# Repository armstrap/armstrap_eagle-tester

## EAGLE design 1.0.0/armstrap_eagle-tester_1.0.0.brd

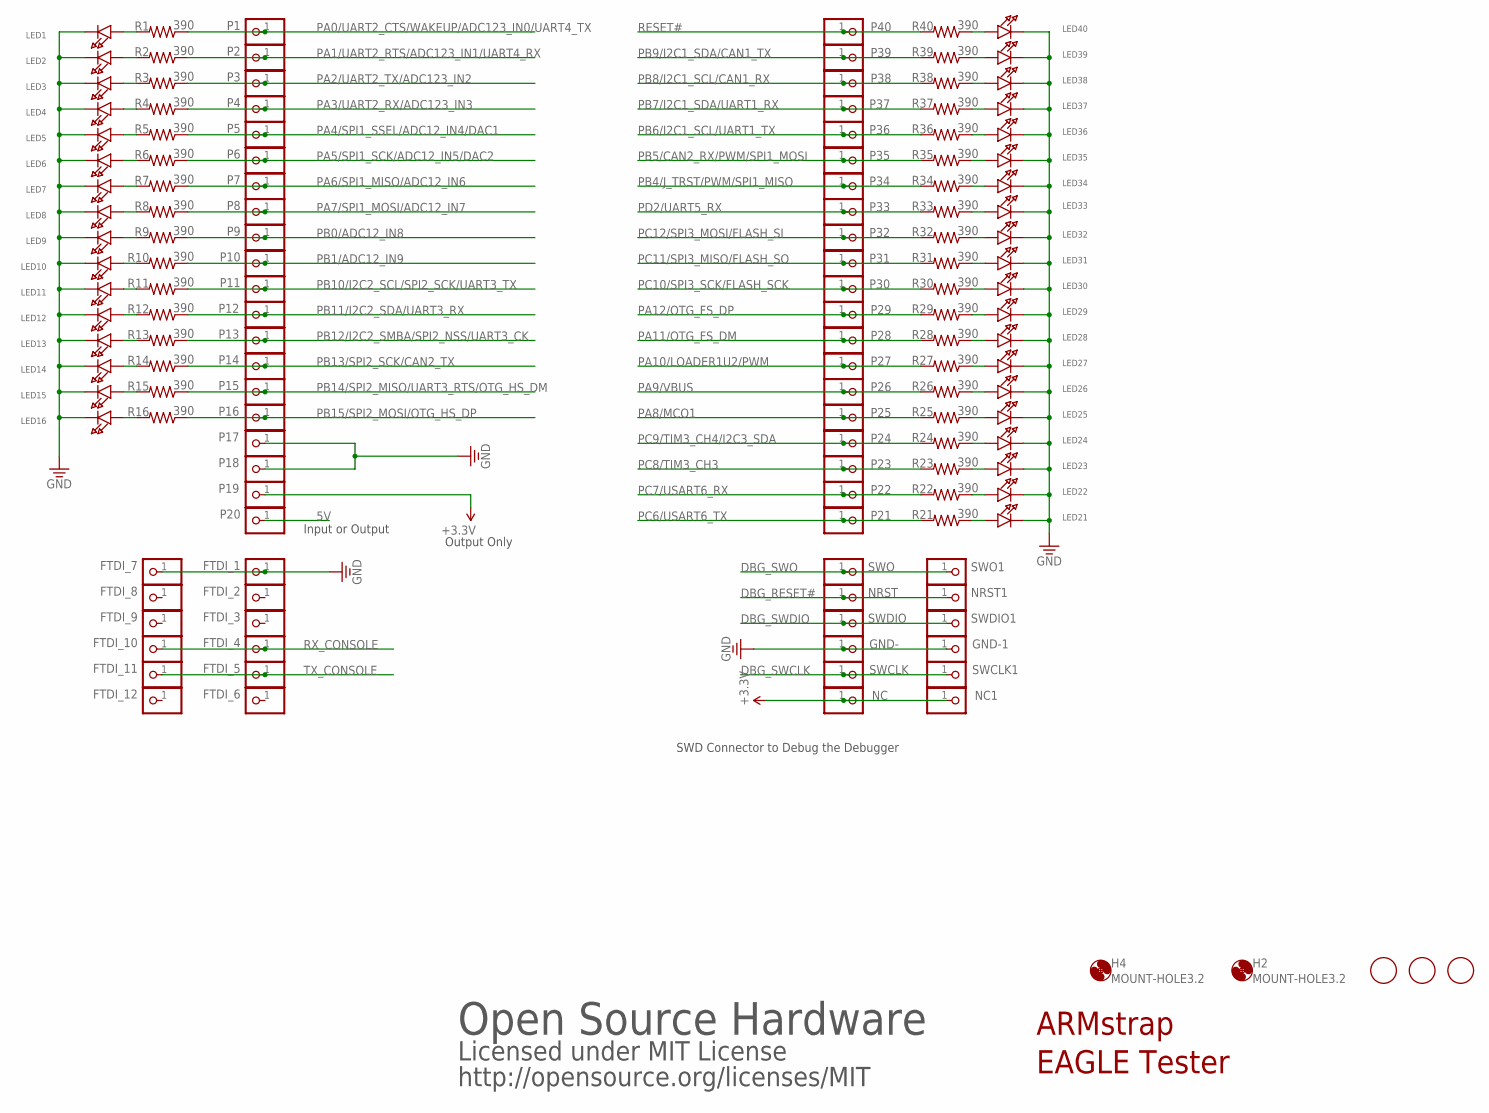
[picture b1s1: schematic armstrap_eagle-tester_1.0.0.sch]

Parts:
FID2, FID3, FID4: FIDUCIAL; FIDUCIAL_1MM
FTDI_1, FTDI_2, FTDI_3, FTDI_4, FTDI_5, FTDI_6, FTDI_7, FTDI_8, FTDI_9, FTDI_10, FTDI_11, FTDI_12: PINHD-1X1; 1X01
GND-, GND-1: PINHD-1X1; 1X01
H2, H4: MOUNT-HOLE3.2; 3,2
LED1, LED2, LED3, LED4, LED5, LED6, LED7, LED8, LED9, LED10, LED11, LED12, LED13, LED14, LED15, LED16, LED21, LED22, LED23, LED24, LED25, LED26, LED27, LED28, LED29, LED30, LED31, LED32, LED33, LED34, LED35, LED36, LED37, LED38, LED39, LED40: APT3216QBC/D; CHIPLED_1206
NC, NC1: PINHD-1X1; 1X01
NRST, NRST1: PINHD-1X1; 1X01
P1, P2, P3, P4, P5, P6, P7, P8, P9, P10, P11, P12, P13, P14, P15, P16, P17, P18, P19, P20, P21, P22, P23, P24, P25, P26, P27, P28, P29, P30, P31, P32, P33, P34, P35, P36, P37, P38, P39, P40: PINHD-1X1; 1X01
R1, R2, R3, R4, R5, R6, R7, R8, R9, R10, R11, R12, R13, R14, R15, R16, R21, R22, R23, R24, R25, R26, R27, R28, R29, R30, R31, R32, R33, R34, R35, R36, R37, R38, R39, R40: 390; 0805
SWCLK, SWCLK1: PINHD-1X1; 1X01
SWDIO, SWDIO1: PINHD-1X1; 1X01
SWO, SWO1: PINHD-1X1; 1X01

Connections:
3.3V: NC.1, NC1.1, P19.1
5: LED5.A, R5.2
5V: P20.1
11: LED11.A, R11.2
DBG_RESET#: NRST.1, NRST1.1
DBG_SWCLK: SWCLK.1, SWCLK1.1
DBG_SWDIO: SWDIO.1, SWDIO1.1
DBG_SWO: SWO.1, SWO1.1
E2: LED2.A, R2.2
GND: FTDI_1.1, FTDI_7.1, GND-.1, GND-1.1, LED1.C, LED2.C, LED3.C, LED4.C, LED5.C, LED6.C, LED7.C, LED8.C, LED9.C, LED10.C, LED11.C, LED12.C, LED13.C, LED14.C, LED15.C, LED16.C, LED21.C, LED22.C, LED23.C, LED24.C, LED25.C, LED26.C, LED27.C, LED28.C, LED29.C, LED30.C, LED31.C, LED32.C, LED33.C, LED34.C, LED35.C, LED36.C, LED37.C, LED38.C, LED39.C, LED40.C, P17.1, P18.1
unnamed: LED1.A, R1.2
unnamed: LED3.A, R3.2
unnamed: LED4.A, R4.2
unnamed: LED6.A, R6.2
unnamed: LED7.A, R7.2
unnamed: LED8.A, R8.2
unnamed: LED9.A, R9.2
unnamed: LED10.A, R10.2
unnamed: LED12.A, R12.2
unnamed: LED13.A, R13.2
unnamed: LED14.A, R14.2
unnamed: LED15.A, R15.2
unnamed: LED16.A, R16.2
unnamed: LED40.A, R40.1
unnamed: LED39.A, R39.1
unnamed: LED38.A, R38.1
unnamed: LED37.A, R37.1
unnamed: LED36.A, R36.1
unnamed: LED35.A, R35.1
unnamed: LED34.A, R34.1
unnamed: LED33.A, R33.1
unnamed: LED32.A, R32.1
unnamed: LED31.A, R31.1
unnamed: LED30.A, R30.1
unnamed: LED29.A, R29.1
unnamed: LED28.A, R28.1
unnamed: LED27.A, R27.1
unnamed: LED26.A, R26.1
unnamed: LED25.A, R25.1
unnamed: LED24.A, R24.1
unnamed: LED23.A, R23.1
unnamed: LED22.A, R22.1
unnamed: LED21.A, R21.1
PA0/UART2_CTS/WAKEUP/ADC123_IN0/UART4_TX: P1.1, R1.1
PA1/UART2_RTS/ADC123_IN1/UART4_RX: P2.1, R2.1
PA2/UART2_TX/ADC123_IN2: P3.1, R3.1
PA3/UART2_RX/ADC123_IN3: P4.1, R4.1
PA4/SPI1_SSEL/ADC12_IN4/DAC1: P5.1, R5.1
PA5/SPI1_SCK/ADC12_IN5/DAC2: P6.1, R6.1
PA6/SPI1_MISO/ADC12_IN6: P7.1, R7.1
PA7/SPI1_MOSI/ADC12_IN7: P8.1, R8.1
PA8/MCO1: P25.1, R25.2
PA9/VBUS: P26.1, R26.2
PA10/LOADER1U2/PWM: P27.1, R27.2
PA11/OTG_FS_DM: P28.1, R28.2
PA12/OTG_FS_DP: P29.1, R29.2
PB0/ADC12_IN8: P9.1, R9.1
PB1/ADC12_IN9: P10.1, R10.1
PB4/J_TRST/PWM/SPI1_MISO: P34.1, R34.2
PB5/CAN2_RX/PWM/SPI1_MOSI: P35.1, R35.2
PB6/I2C1_SCL/UART1_TX: P36.1, R36.2
PB7/I2C1_SDA/UART1_RX: P37.1, R37.2
PB8/I2C1_SCL/CAN1_RX: P38.1, R38.2
PB9/I2C1_SDA/CAN1_TX: P39.1, R39.2
PB10/I2C2_SCL/SPI2_SCK/UART3_TX: P11.1, R11.1
PB11/I2C2_SDA/UART3_RX: P12.1, R12.1
PB12/I2C2_SMBA/SPI2_NSS/UART3_CK: P13.1, R13.1
PB13/SPI2_SCK/CAN2_TX: P14.1, R14.1
PB14/SPI2_MISO/UART3_RTS/OTG_HS_DM: P15.1, R15.1
PB15/SPI2_MOSI/OTG_HS_DP: P16.1, R16.1
PC6/USART6_TX: P21.1, R21.2
PC7/USART6_RX: P22.1, R22.2
PC8/TIM3_CH3: P23.1, R23.2
PC9/TIM3_CH4/I2C3_SDA: P24.1, R24.2
PC10/SPI3_SCK/FLASH_SCK: P30.1, R30.2
PC11/SPI3_MISO/FLASH_SO: P31.1, R31.2
PC12/SPI3_MOSI/FLASH_SI: P32.1, R32.2
PD2/UART5_RX: P33.1, R33.2
RESET#: P40.1, R40.2
RX_CONSOLE: FTDI_4.1, FTDI_10.1
TX_CONSOLE: FTDI_5.1, FTDI_11.1

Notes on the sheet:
ARMstrap
Open Source Hardware
Licensed under MIT License
http://opensource.org/licenses/MIT
SWD Connector to Debug the Debugger
EAGLE Tester
Input or Output
Output Only

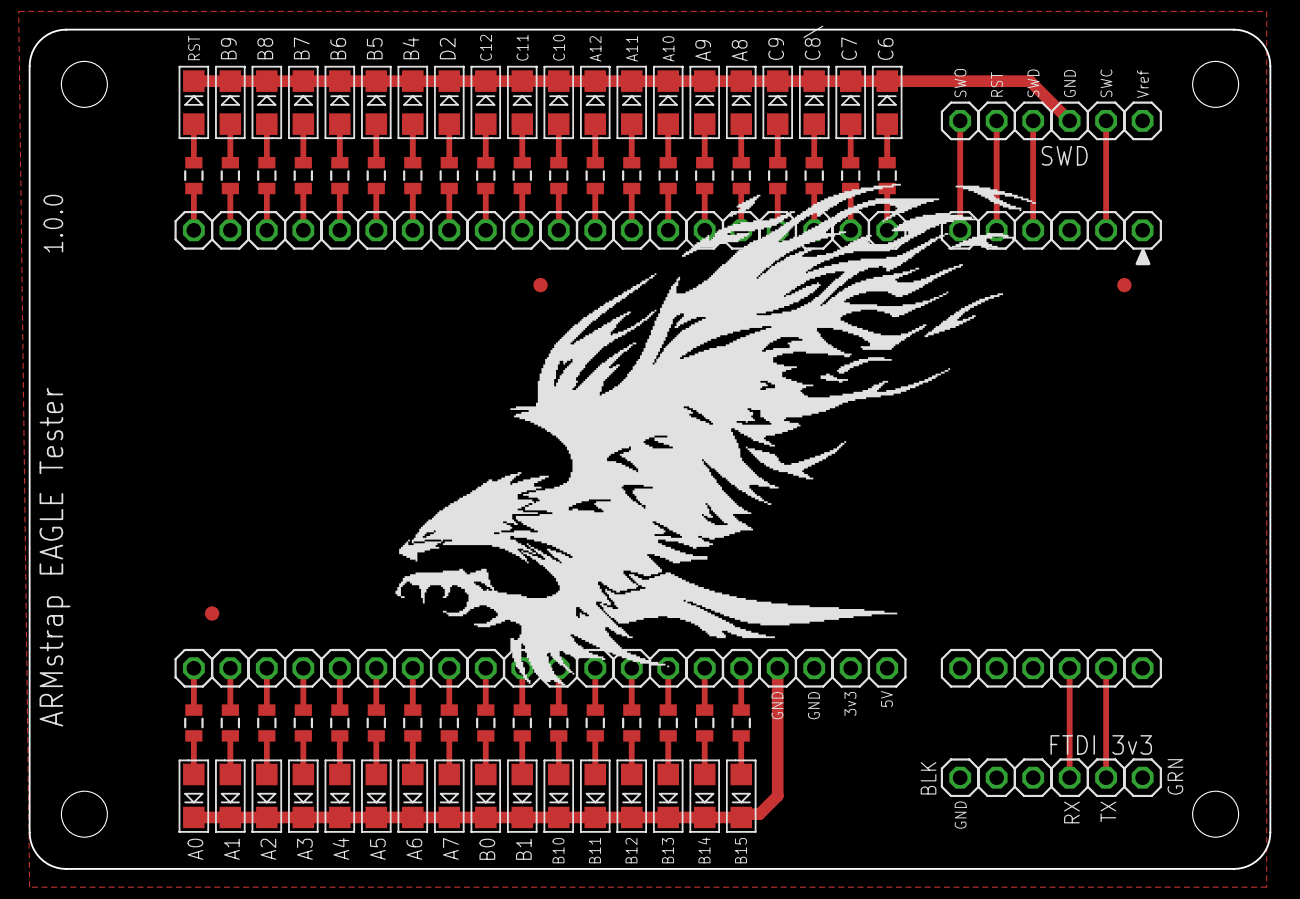
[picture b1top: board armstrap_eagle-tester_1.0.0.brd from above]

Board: 2 copper layers, 86.4 x 58.4 mm, 143 parts (0 on the bottom side), 80 nets.

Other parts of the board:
H1, H3: MOUNT-HOLE3.2; 3,2

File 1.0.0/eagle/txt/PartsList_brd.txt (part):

Partlist

Exported from armstrap_eagle-tester_1.0.0.brd at 12/7/14 9:47 PM

EAGLE Version 6.4.0 Copyright (c) 1988-2013 CadSoft

Assembly variant: 

Part     Value          Package      Library  Position (inch)       Orientation

FID2     FIDUCIAL       FIDUCIAL_1MM vovtech  (3 1.6)               R0
FID3     FIDUCIAL       FIDUCIAL_1MM vovtech  (0.5 0.7)             R0
FID4     FIDUCIAL       FIDUCIAL_1MM vovtech  (1.4 1.6)             R0
FTDI_1                  1X01         pinhead  (2.55 0.55)           R0
FTDI_2                  1X01         pinhead  (2.65 0.55)           R0
FTDI_3                  1X01         pinhead  (2.75 0.55)           R0
FTDI_4                  1X01         pinhead  (2.85 0.55)           R0
FTDI_5                  1X01         pinhead  (2.95 0.55)           R0
FTDI_6                  1X01         pinhead  (3.05 0.55)           R0
FTDI_7                  1X01         pinhead  (2.55 0.25)           R90
FTDI_8                  1X01         pinhead  (2.65 0.25)           R90
FTDI_9                  1X01         pinhead  (2.75 0.25)           R90
FTDI_10                 1X01         pinhead  (2.85 0.25)           R90
FTDI_11                 1X01         pinhead  (2.95 0.25)           R90
FTDI_12                 1X01         pinhead  (3.05 0.25)           R90
GND-                    1X01         pinhead  (2.85 1.75)           R0
GND-1                   1X01         pinhead  (2.85 2.05)           R90
LED1     APT3216QBC/D   CHIPLED_1206 vovtech  (0.45 0.2)            R90
LED2     APT3216QBC/D   CHIPLED_1206 vovtech  (0.55 0.2)            R90
LED3     APT3216QBC/D   CHIPLED_1206 vovtech  (0.65 0.2)            R90
LED4     APT3216QBC/D   CHIPLED_1206 vovtech  (0.75 0.2)            R90
LED5     APT3216QBC/D   CHIPLED_1206 vovtech  (0.85 0.2)            R90
LED6     APT3216QBC/D   CHIPLED_1206 vovtech  (0.95 0.2)            R90
LED7     APT3216QBC/D   CHIPLED_1206 vovtech  (1.05 0.2)            R90
LED8     APT3216QBC/D   CHIPLED_1206 vovtech  (1.15 0.2)            R90
LED9     APT3216QBC/D   CHIPLED_1206 vovtech  (1.25 0.2)            R90
LED10    APT3216QBC/D   CHIPLED_1206 vovtech  (1.35 0.2)            R90
LED11    APT3216QBC/D   CHIPLED_1206 vovtech  (1.45 0.2)            R90
LED12    APT3216QBC/D   CHIPLED_1206 vovtech  (1.55 0.2)            R90
LED13    APT3216QBC/D   CHIPLED_1206 vovtech  (1.65 0.2)            R90
LED14    APT3216QBC/D   CHIPLED_1206 vovtech  (1.75 0.2)            R90
LED15    APT3216QBC/D   CHIPLED_1206 vovtech  (1.85 0.2)            R90
LED16    APT3216QBC/D   CHIPLED_1206 vovtech  (1.95 0.2)            R90
LED21    APT3216QBC/D   CHIPLED_1206 vovtech  (2.35 2.1)            R270
LED22    APT3216QBC/D   CHIPLED_1206 vovtech  (2.25 2.1)            R270
LED23    APT3216QBC/D   CHIPLED_1206 vovtech  (2.15 2.1)            R270
LED24    APT3216QBC/D   CHIPLED_1206 vovtech  (2.05 2.1)            R270
LED25    APT3216QBC/D   CHIPLED_1206 vovtech  (1.95 2.1)            R270
LED26    APT3216QBC/D   CHIPLED_1206 vovtech  (1.85 2.1)            R270
LED27    APT3216QBC/D   CHIPLED_1206 vovtech  (1.75 2.1)            R270
LED28    APT3216QBC/D   CHIPLED_1206 vovtech  (1.65 2.1)            R270
LED29    APT3216QBC/D   CHIPLED_1206 vovtech  (1.55 2.1)            R270
LED30    APT3216QBC/D   CHIPLED_1206 vovtech  (1.45 2.1)            R270
LED31    APT3216QBC/D   CHIPLED_1206 vovtech  (1.35 2.1)            R270
LED32    APT3216QBC/D   CHIPLED_1206 vovtech  (1.25 2.1)            R270
LED33    APT3216QBC/D   CHIPLED_1206 vovtech  (1.15 2.1)            R270
LED34    APT3216QBC/D   CHIPLED_1206 vovtech  (1.05 2.1)            R270
LED35    APT3216QBC/D   CHIPLED_1206 vovtech  (0.95 2.1)            R270
LED36    APT3216QBC/D   CHIPLED_1206 vovtech  (0.85 2.1)            R270
LED37    APT3216QBC/D   CHIPLED_1206 vovtech  (0.75 2.1)            R270
LED38    APT3216QBC/D   CHIPLED_1206 vovtech  (0.65 2.1)            R270
LED39    APT3216QBC/D   CHIPLED_1206 vovtech  (0.55 2.1)            R270
LED40    APT3216QBC/D   CHIPLED_1206 vovtech  (0.45 2.1)            R270
NC                      1X01         pinhead  (3.05 1.75)           R0
NC1                     1X01         pinhead  (3.05 2.05)           R90
NRST                    1X01         pinhead  (2.65 1.75)           R0
NRST1                   1X01         pinhead  (2.65 2.05)           R90
P1                      1X01         pinhead  (0.45 0.55)           R0
P2                      1X01         pinhead  (0.55 0.55)           R90
P3                      1X01         pinhead  (0.65 0.55)           R90
P4                      1X01         pinhead  (0.75 0.55)           R90
P5                      1X01         pinhead  (0.85 0.55)           R90
P6                      1X01         pinhead  (0.95 0.55)           R90
P7                      1X01         pinhead  (1.05 0.55)           R90
P8                      1X01         pinhead  (1.15 0.55)           R90
P9                      1X01         pinhead  (1.25 0.55)           R90
P10                     1X01         pinhead  (1.35 0.55)           R90
P11                     1X01         pinhead  (1.45 0.55)           R90
P12                     1X01         pinhead  (1.55 0.55)           R90
P13                     1X01         pinhead  (1.65 0.55)           R90
P14                     1X01         pinhead  (1.75 0.55)           R90
P15                     1X01         pinhead  (1.85 0.55)           R90
P16                     1X01         pinhead  (1.95 0.55)           R90
P17                     1X01         pinhead  (2.05 0.55)           R90
P18                     1X01         pinhead  (2.15 0.55)           R90
P19                     1X01         pinhead  (2.25 0.55)           R90
P20                     1X01         pinhead  (2.35 0.55)           R90
P21                     1X01         pinhead  (2.35 1.75)           R0
P22                     1X01         pinhead  (2.25 1.75)           R0
P23                     1X01         pinhead  (2.15 1.75)           R0
P24                     1X01         pinhead  (2.05 1.75)           R0
P25                     1X01         pinhead  (1.95 1.75)           R0
P26                     1X01         pinhead  (1.85 1.75)           R0
P27                     1X01         pinhead  (1.75 1.75)           R0
P28                     1X01         pinhead  (1.65 1.75)           R0
P29                     1X01         pinhead  (1.55 1.75)           R0
P30                     1X01         pinhead  (1.45 1.75)           R0
P31                     1X01         pinhead  (1.35 1.75)           R0
P32                     1X01         pinhead  (1.25 1.75)           R0
P33                     1X01         pinhead  (1.15 1.75)           R0
P34                     1X01         pinhead  (1.05 1.75)           R0
P35                     1X01         pinhead  (0.95 1.75)           R0
P36                     1X01         pinhead  (0.85 1.75)           R0
P37                     1X01         pinhead  (0.75 1.75)           R0
P38                     1X01         pinhead  (0.65 1.75)           R0
P39                     1X01         pinhead  (0.55 1.75)           R0
P40                     1X01         pinhead  (0.45 1.75)           R0
R1       390            0805         vovtech  (0.45 0.4)            R270
R2       390            0805         vovtech  (0.55 0.4)            R270
R3       390            0805         vovtech  (0.65 0.4)            R270
R4       390            0805         vovtech  (0.75 0.4)            R270
R5       390            0805         vovtech  (0.85 0.4)            R270
R6       390            0805         vovtech  (0.95 0.4)            R270
R7       390            0805         vovtech  (1.05 0.4)            R270
R8       390            0805         vovtech  (1.15 0.4)            R270
R9       390            0805         vovtech  (1.25 0.4)            R270
R10      390            0805         vovtech  (1.35 0.4)            R270
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
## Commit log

2014-12-08 Adding Eagle Tester files

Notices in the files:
parts and their libraries:
vovtech: Licensing: CC v3.0 Share-Alike You are welcome to use this library for commercial purposes.
